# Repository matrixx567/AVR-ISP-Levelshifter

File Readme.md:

# Levelshifter for AVR ISP Programmer

This board converts the ISP programming signals between a 5V ISP programmer and a
3.3V supplied board.

## License

This work by Martin Nöhrer is licensed under a [Creative Commons Attribution-ShareAlike 4.0 International License](http://creativecommons.org/licenses/by-sa/4.0/).

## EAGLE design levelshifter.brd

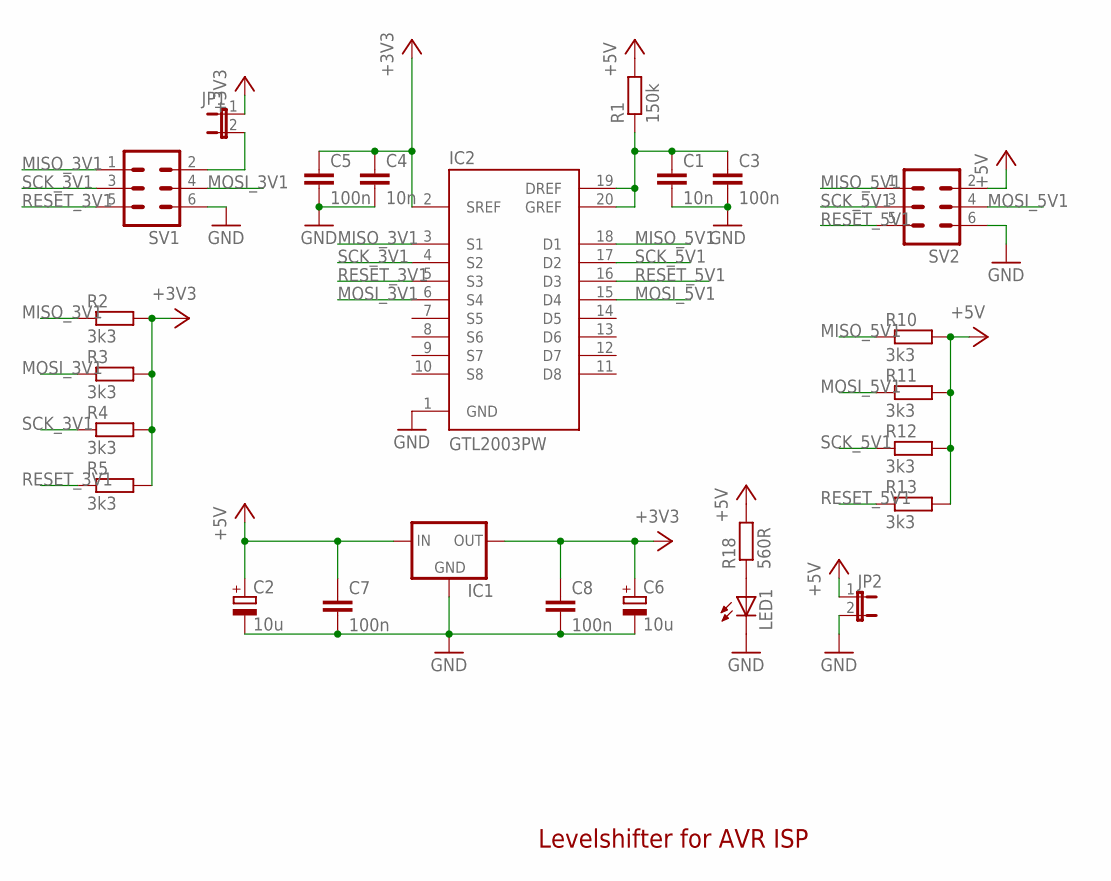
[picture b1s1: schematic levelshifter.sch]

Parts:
C1, C4: 10n; C1206
C2, C6: 10u; SMC_C
C3, C5, C7, C8: 100n; C1206
IC1: LM1117; SOT223
IC2: GTL2003PW; TSSOP20
JP1, JP2: JP1E; JP1
LED1: LEDSMT1206; 1206
R1: 150k; R1206
R2, R3, R4, R5, R10, R11, R12, R13: 3k3; R1206
R18: 560R; R1206
SV1, SV2: ML6

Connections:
+3V3: C4.1, C5.1, C6.+, C8.1, IC1.2 (OUT), IC2.2 (SREF), JP1.1, R2.2, R3.2, R4.2, R5.2
+5V: C2.+, C7.1, IC1.3 (IN), JP2.1, R1.2, R10.2, R11.2, R12.2, R13.2, R18.2, SV2.2
GND: C1.2, C2.-, C3.2, C4.2, C5.2, C6.-, C7.2, C8.2, IC1.1 (GND), IC2.1 (GND), JP2.2, LED1.C, SV1.6, SV2.6
MISO_3V1: IC2.3 (S1), R2.1, SV1.1
MISO_5V1: IC2.18 (D1), R10.1, SV2.1
MOSI_3V1: IC2.6 (S4), R3.1, SV1.4
MOSI_5V1: IC2.15 (D4), R11.1, SV2.4
unnamed: JP1.2, SV1.2
unnamed: C1.1, C3.1, IC2.19 (DREF), IC2.20 (GREF), R1.1
unnamed: LED1.A, R18.1
RESET_3V1: IC2.5 (S3), R5.1, SV1.5
RESET_5V1: IC2.16 (D3), R13.1, SV2.5
SCK_3V1: IC2.4 (S2), R4.1, SV1.3
SCK_5V1: IC2.17 (D2), R12.1, SV2.3

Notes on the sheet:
Levelshifter for AVR ISP

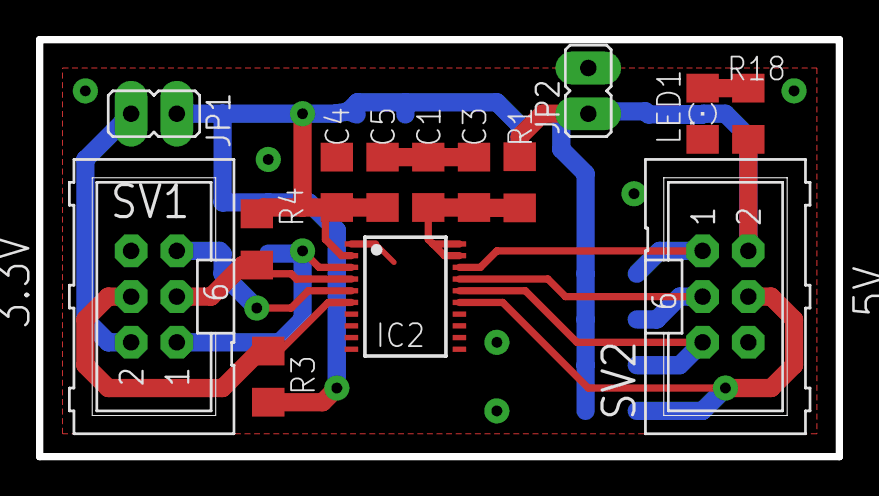
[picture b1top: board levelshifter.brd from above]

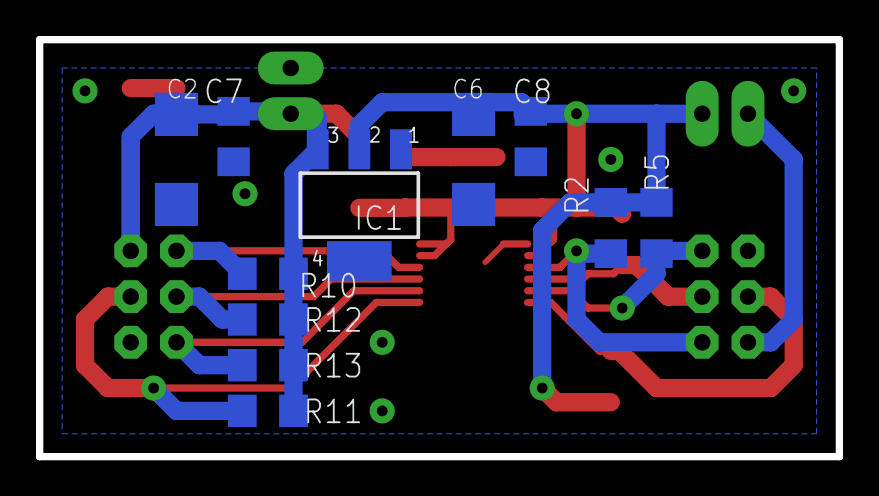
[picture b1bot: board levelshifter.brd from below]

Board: 2 copper layers, 44.4 x 23.2 mm, 25 parts (11 on the bottom side), 14 nets.

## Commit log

2015-09-26 add board description
